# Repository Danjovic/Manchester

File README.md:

# Manchester
Enhanced MasterPlay alike adapter for Atari 5200 that provides start and pause buttons with minimal parts count. 

## Button Mapping

## PCB

## Schematic

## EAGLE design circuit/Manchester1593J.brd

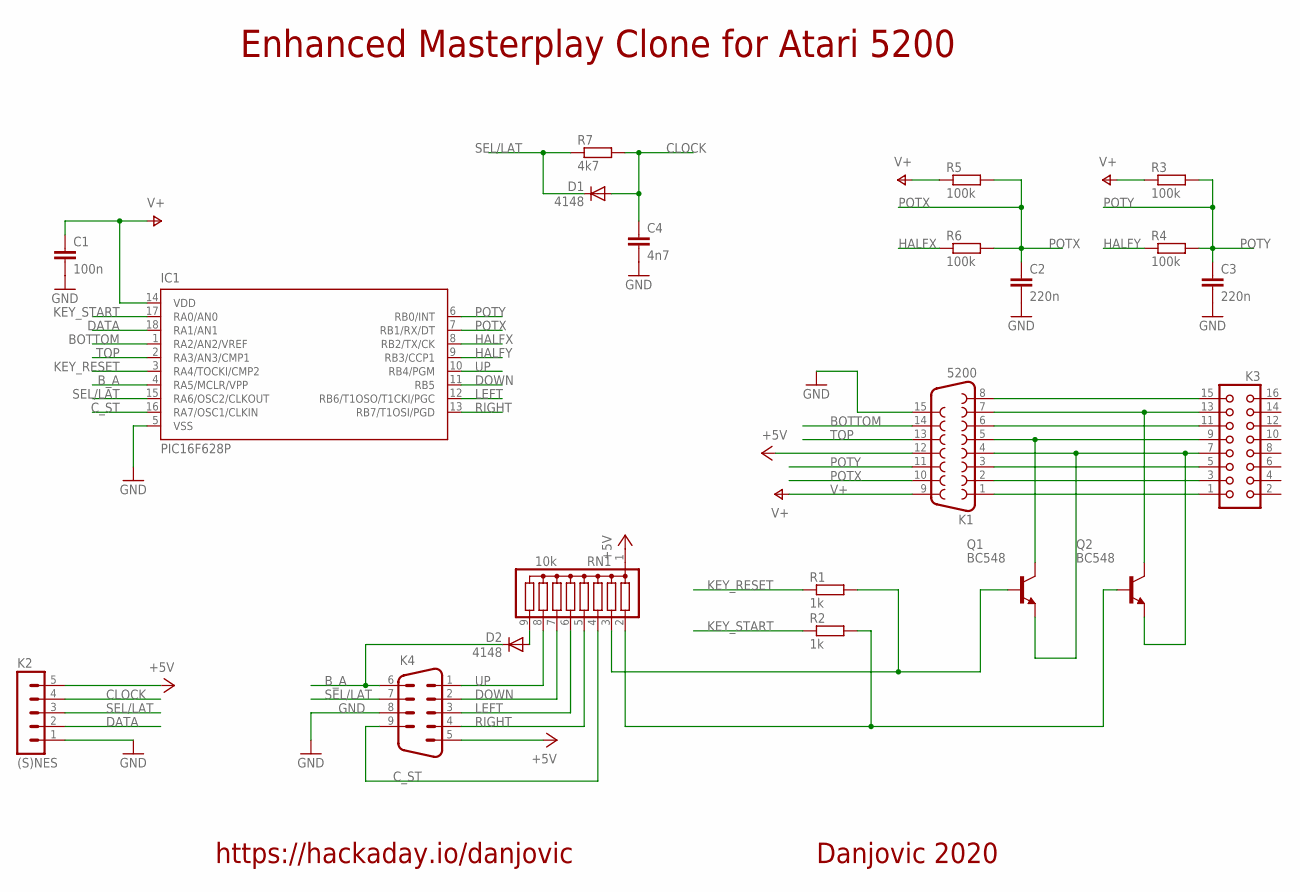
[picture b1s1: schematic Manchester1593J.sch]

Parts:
C1: 100n; C050-024X044
C2, C3: 220n; C050-024X044
C4: 4n7; C050-024X044
D1, D2: 4148; D-5
IC1: PIC16F628P; DIL18
K1: 5200; F15H
K2: (S)NES; MA05-1
K3: CON16L
K4: M09H
Q1, Q2: BC548; TO92
R1, R2: 1k; 0204/7
R3, R4, R5, R6: 100k; 0204/7
R7: 4k7; 0204/7
RN1: 10k; SIL9

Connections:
+5V: K1.12, K2.5, K4.5, RN1.1
BOTTOM: IC1.1 (RA2/AN2/VREF), K1.14
B_A: D2.C, IC1.4 (RA5/MCLR/VPP), K4.6
CLOCK: C4.1, D1.A, K2.4, R7.2
COL0: K1.7, K3.13, Q2.3 (C)
COL1: K1.6, K3.11
COL2: K1.5, K3.9, Q1.3 (C)
COL3: K1.8, K3.15
C_ST: IC1.16 (RA7/OSC1/CLKIN), K4.9, RN1.4
DATA: IC1.18 (RA1/AN1), K2.2
DOWN: IC1.11 (RB5), K4.2, RN1.7
GND: C1.2, C2.2, C3.2, C4.2, IC1.5 (VSS), K1.15, K2.1, K4.8
HALFX: IC1.8 (RB2/TX/CK), R6.1
HALFY: IC1.9 (RB3/CCP1), R4.1
KEY_RESET: IC1.3 (RA4/TOCKI/CMP2), R1.1
KEY_START: IC1.17 (RA0/AN0), R2.1
LEFT: IC1.12 (RB6/T1OSO/T1CKI/PGC), K4.3, RN1.6
unnamed: Q1.2 (B), R1.2, RN1.3
unnamed: Q2.2 (B), R2.2, RN1.2
unnamed: D2.A, RN1.9
POTX: C2.1, IC1.7 (RB1/RX/DT), K1.10, R5.2, R6.2
POTY: C3.1, IC1.6 (RB0/INT), K1.11, R3.2, R4.2
RIGHT: IC1.13 (RB7/T1OSI/PGD), K4.4, RN1.5
ROW0: K1.3, K3.5
ROW1: K1.2, K3.3
ROW2: K1.1, K3.1
ROW3: K1.4, K3.7, Q1.1 (E), Q2.1 (E)
SEL/LAT: D1.C, IC1.15 (RA6/OSC2/CLKOUT), K2.3, K4.7, R7.1
TOP: IC1.2 (RA3/AN3/CMP1), K1.13
UP: IC1.10 (RB4/PGM), K4.1, RN1.8
V+: C1.1, IC1.14 (VDD), K1.9, R3.1, R5.1

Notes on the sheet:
Enhanced Masterplay Clone for Atari 5200
Danjovic 2020
https://hackaday.io/danjovic

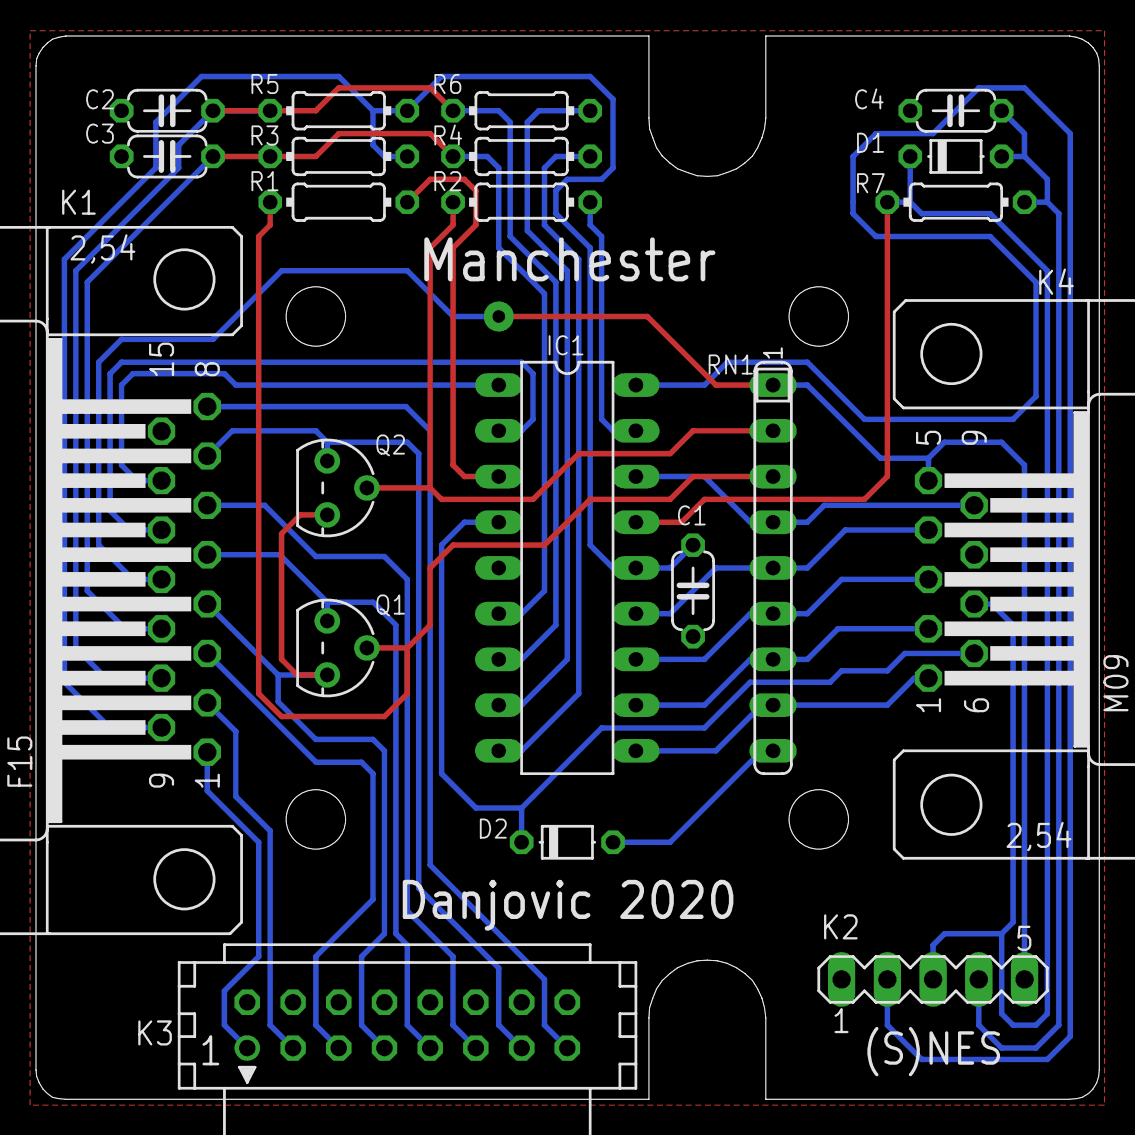
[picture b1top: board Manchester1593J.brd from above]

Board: 2 copper layers, 59.1 x 59.1 mm, 22 parts (0 on the bottom side), 31 nets.

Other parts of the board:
U$1: 1593J

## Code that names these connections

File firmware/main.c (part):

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///                                                                                                         ///
///////////////////////////////////////////////////////////////////////////////////////////////////////////////

uint16_t __at _CONFIG configWord = _INTRC_OSC_NOCLKOUT & // internal RC oscillator, IO on pins RA4/5
                                   _CPD_OFF &            // data protecion off
                                   _MCLRE_OFF &          // pin MCLR as IO, internal reset
                                   _CP_OFF   &           // code protection off
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#define TRIS_SELLAT TRISA6
#define TRIS_CSTART TRISA7
					
#define PIN_START   RA0
#define PIN_DATAIN  RA1
#define PIN_BOTTOM	RA2			
#define PIN_TOP     RA3
#define PIN_PAUSE   RA4
#define PIN_B_A     RA5
#define PIN_C_ST    RA6
#define PIN_SEL_LAT RA7
					
#define PIN_POTY    RB0
#define PIN_POTX    RB1
#define PIN_HALFX   RB2
#define PIN_HALFY   RB3
#define PIN_UP      RB4
#define PIN_DOWN    RB5
#define PIN_LEFT    RB6
#define PIN_RIGHT   RB7


#define setLatClkLow()  PIN_SEL_LAT=0
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#define dataIn() ( PIN_DATAIN == 0 )

#define _TRGA  (1<<0)  //      _____                                                     _____
#define _TRGB  (1<<1)  // LAT       \___________________________________________________/
#define _SEL   (1<<2)  //      _____                                                     ______
#define _STRT  (1<<3)  // CLK       \_______/\____/\____/\____/\____/\____/\____/\____/\/
#define _UP    (1<<4)  // 
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#define pinDOWN()   ( PIN_DOWN  == 0 )
#define pinLEFT()   ( PIN_LEFT  == 0 )
#define pinRIGHT()  ( PIN_RIGHT == 0 )
#define pinBA()     ( PIN_B_A   ==0  )
#define pinCSTART() ( PIN_C_ST  == 0 )

#define fire1Low()  do { TRIS_TOP    = 0; PIN_TOP    = 0; } while (0)
#define fire1Open() do { TRIS_TOP    = 1; PIN_TOP    = 1; } while (0)
#define fire2Low()  do { TRIS_BOTTOM = 0; PIN_BOTTOM = 0; } while (0)
#define fire2Open() do { TRIS_BOTTOM = 1; PIN_BOTTOM = 1; } while (0)

#define setKeySel()       PIN_PAUSE = 1
#define releaseKeySel()   PIN_PAUSE = 0
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#define releaseKeyStart() PIN_START = 0


#define set_X_left()      do { TRIS_HALFX = 1; TRIS_POTX = 0; PIN_HALFX = 0; PIN_POTX = 1; } while (0)  // minimum resistance
#define set_X_middle()    do { TRIS_HALFX = 0; TRIS_POTX = 1; PIN_HALFX = 1; PIN_POTX = 0; } while (0)
#define set_X_right()     do { TRIS_HALFX = 1; TRIS_POTX = 1; PIN_HALFX = 0; PIN_POTX = 0; } while (0)  

#define set_Y_north()     do { TRIS_HALFY = 1; TRIS_POTY = 0; PIN_HALFY = 0; PIN_POTY = 1; } while (0)  // minumum resistance
#define set_Y_middle()    do { TRIS_HALFY = 0; TRIS_POTY = 1; PIN_HALFY = 1; PIN_POTY = 0; } while (0)
#define set_Y_south()     do { TRIS_HALFY = 1; TRIS_POTY = 1; PIN_HALFY = 0; PIN_POTY = 0; } while (0)

#define delay5us()        do { __asm__("nop\n nop\n nop\n nop\n nop"); } while (0)
#define delay4us()        do { __asm__("nop\n nop\n nop\n nop"); } while (0)
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
  PIN_START   = 0; // Key Start unactive
  PIN_DATAIN  = 0; // 
  PIN_BOTTOM  = 1; // 			
  PIN_TOP     = 1; // 
  PIN_PAUSE   = 0; // Key Pause unactive
  PIN_B_A     = 0; // 
  PIN_SEL_LAT = 1; // Set LATCH/CLOCK in "HIGH"
  PIN_C_ST    = 0; // 

  TRIS_POTY   = 1; // Y axis at middle
  TRIS_HALFY  = 0; // 
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  TRIS_LEFT   = 1; // Genesis LEFT as input
  TRIS_RIGHT  = 1; // Genesis RIGHT as input
 
  PIN_POTY    = 0; // Y axis at middle
  PIN_HALFY   = 1; //   
  PIN_POTX    = 0; // X axis at middle
  PIN_HALFX   = 1; // 

  PIN_UP      = 0; // No pullups
  PIN_DOWN    = 0; //  
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
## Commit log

2020-10-04 Added PCB for Hammond 1593J case

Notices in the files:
firmware/main.c:
This program is free software: you can redistribute it and/or modify
it under the terms of the GNU General Public License as published by
the Free Software Foundation, either version 3 of the License, or
(at your option) any later version.
parts and their libraries:
SparkFun-Aesthetics: Licensing: Creative Commons ShareAlike 4.0 International - https://creativecommons.org/licenses/by-sa/4.0
